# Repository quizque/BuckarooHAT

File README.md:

# BuckarooHAT
FRC Raspberry Pi Passive PoE Hat

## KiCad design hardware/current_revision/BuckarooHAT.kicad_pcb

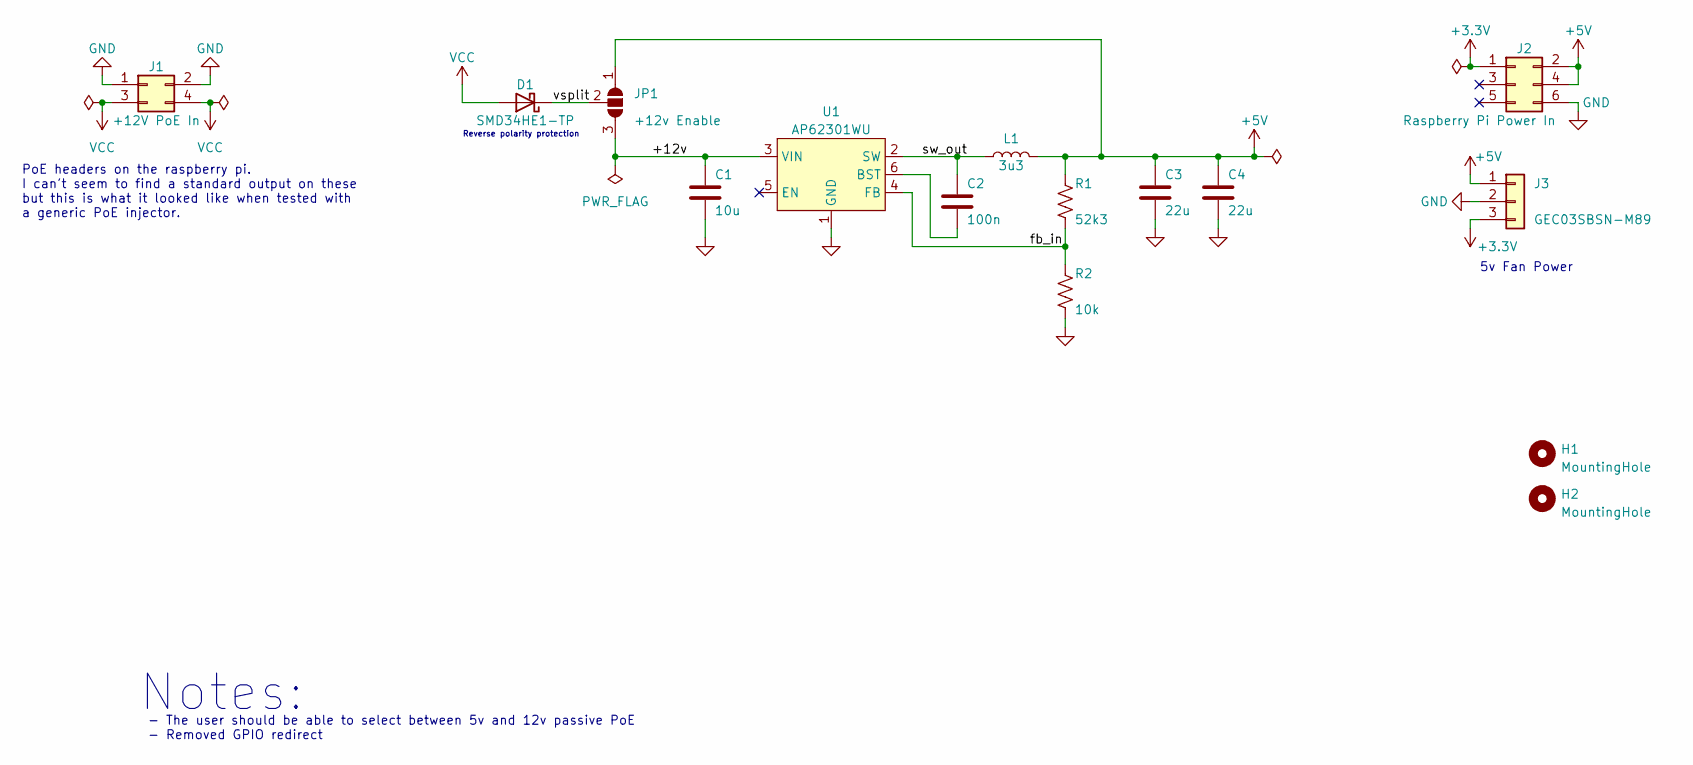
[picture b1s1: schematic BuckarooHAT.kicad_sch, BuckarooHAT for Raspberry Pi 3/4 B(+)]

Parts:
C1: 10u; C_0805_2012Metric_Pad1.18x1.45mm_HandSolder
C2: 100n; C_0603_1608Metric_Pad1.08x0.95mm_HandSolder
C3, C4: 22u; C_0603_1608Metric_Pad1.08x0.95mm_HandSolder
D1: SMD34HE1-TP
H1, H2: MountingHole; MountingHole_2.7mm_M2.5_ISO7380_Pad_TopBottom
J1: +12V PoE In; RS2BE-04-G-SMT
J2: Raspberry Pi Power In; RS2BE-06-G-SMT
J3: GEC03SBSN-M89
JP1: +12v Enable; SolderJumper-3_P1.3mm_Open_RoundedPad1.0x1.5mm_NumberLabels
L1: 3u3; L_Taiyo-Yuden_NR-50xx_HandSoldering
R1: 52k3; R_0603_1608Metric_Pad0.98x0.95mm_HandSolder
R2: 10k; R_0603_1608Metric_Pad0.98x0.95mm_HandSolder
U1: AP62301WU; SOT-23-6

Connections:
+3.3V: J2.1, J3.3
+5V: C3.1, C4.1, J2.2, J2.4, J3.1, JP1.1 (A), L1.2, R1.1
/+12v: C1.1, JP1.3 (B), U1.3 (VIN)
/fb_in: R1.2, R2.1, U1.4 (FB)
/sw_out: C2.1, L1.1, U1.2 (SW)
/vsplit: D1.1 (K), JP1.2 (C)
GND: C1.2, C3.2, C4.2, J1.1, J1.2, J2.6, J3.2, R2.2, U1.1 (GND)
unnamed: C2.2, U1.6 (BST)
VCC: D1.2 (A), J1.3, J1.4

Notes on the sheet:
PoE headers on the raspberry pi. I can't seem to find a standard output on these but this is what it looked like when tested with a generic PoE injector.
Reverse polarity protection
- The user should be able to select between 5v and 12v passive PoE - Removed GPIO redirect
5v Fan Power
Notes:

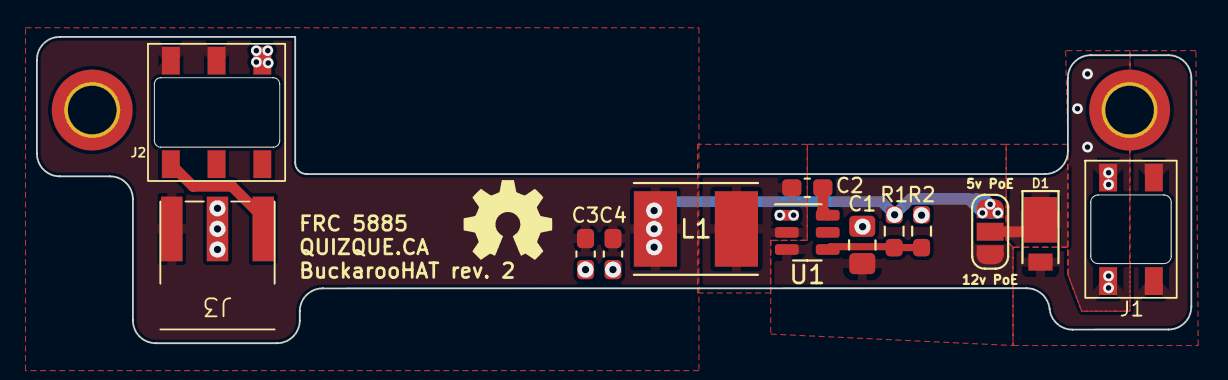
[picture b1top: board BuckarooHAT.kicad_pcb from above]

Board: 2 copper layers, 64.1 x 17.0 mm, 15 parts (0 on the bottom side), 9 nets.

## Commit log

2023-03-29 Initial Push
2023-03-29 Added gitignore
2023-04-04 Update board colors
2023-04-12 Fixed footprint for buck
    How did this happen???
